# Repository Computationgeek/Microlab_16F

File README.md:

# MicroLab 16F - PIC16F877A Development Board  
A hand-soldered PIC16F877A development board built entirely on perfboard. This project was born from a desire to gain a deep understanding of embedded systems hardware by building everything from scratch - no pre-made modules, no shortcuts.

## Vision & Motivation

In 2026, most developers rely on modern MCUs like ESP32 and STM32. But there's something special about PIC microcontrollers - they force you to understand registers, bit manipulation, and hardware at a fundamental level: no HAL abstraction, no hand-holding.

I built MicroLab 16F because:
- **Learning by doing** - Soldering each connection taught me more than any tutorial
- **Legacy matters** - PIC16F877A is still widely used in education and industry
- **Maker ethos** - If you can't build it yourself, you don't truly understand it
- **Fun over perfection** - This isn't a product, it's a learning journey

## Features

### Hardware
- **PIC16F877A** microcontroller (40-pin DIP)
- **20MHz HS crystal** oscillator with 22pF load capacitors
- **Mini breadboard** integrated prototyping area
- **10kΩ potentiometer** connected to RA0 (ADC input)
- **Active buzzer** driven by BC547 NPN transistor on RD1
- **User-addressable LED** on RB0
- **Two tactile buttons** - User button (configurable) and Reset button (MCLR)
- **USB-C power input** with 5V regulation
- **PICkit3 programming header** (ICSP interface)
- **Labeled pin headers** for all GPIO ports (PORTA, PORTB, PORTC, PORTD, PORTE)

### Power System
- USB-C input with 5V output
- Dedicated power LED indicator
- Decoupling capacitors for stable operation
- External power compatible (PICkit3 or USB-C)

## Detailed Specifications

| Parameter | Value |
|-----------|-------|
| **Microcontroller** | PIC16F877A (Microchip) |
| **Architecture** | 8-bit RISC |
| **Program Memory** | 14.3 KB (8192 words) Flash |
| **RAM** | 368 bytes |
| **EEPROM** | 256 bytes |
| **Clock Frequency** | 20 MHz (HS Crystal) |
| **I/O Pins** | 33 |
| **ADC Channels** | 8 (10-bit resolution) |
| **Timers** | 3 (Timer0/1/2) |
| **PWM Channels** | 2 (CCP modules) |
| **Serial Interfaces** | USART, I²C, SPI |
| **Operating Voltage** | 5V DC |
| **Power Source** | USB-C (5V) |
| **Programming Interface** | ICSP (In-Circuit Serial Programming) |
| **Programmer** | PICkit3

## Components Used

### Main Components
| Component | Specification | Quantity | Purpose |
|-----------|---------------|----------|---------|
| PIC16F877A-I/P | 40-pin DIP | 1 | Main microcontroller |
| Crystal Oscillator | 20 MHz HC-49S | 1 | Clock source |
| Ceramic Capacitor | 22pF | 2 | Crystal load capacitors |
| Ceramic Capacitor | 100nF | 5+ | Decoupling/bypass |
| Electrolytic Capacitor | 10µF 16V | 2 | Power filtering |
| BC547 NPN Transistor | TO-92 | 1 | Buzzer driver |
| Active Buzzer | 5V | 1 | Audio output |
| LED (5mm) | Red/Green | 3 | Power, User, Status indicators |
| Resistor | 10kΩ | 5+ | Pull-ups, current limiting |
| Resistor | 330Ω | 3 | LED current limiting |
| Resistor | 1kΩ | 1 | Base resistor for BC547 |
| Potentiometer | 10kΩ linear | 1 | Analog input (RA0) |
| Tactile Switch | 6×6mm | 2 | User button, Reset button |
| Mini Breadboard | 170 points | 1 | Prototyping area |
| USB-C Connector | Breakout module | 1 | Power input |
| Pin Headers | 2.54mm pitch | Multiple | GPIO breakout |
| Perfboard | Single-sided | 1 | PCB substrate |
| IC Socket | 40-pin DIP | 1 | PIC mounting (optional) |

## Software & Tools

### Development Environment
- **IDE:** MPLAB X IDE v6.20 (Last version with PICkit3 support)
- **Compiler:** MPLAB XC8 v2.46 (Free edition)
- **Programmer:** PICkit3 In-Circuit Debugger/Programmer
- **OS:** Tested on Linux Mint 21.3 & Windows 10/11

### Programming Setup
```bash
# Linux users: Add udev rules for PICkit3
sudo nano /etc/udev/rules.d/26-microchip.rules

# Add this line:
SUBSYSTEM=="usb", ATTR{idVendor}=="04d8", ATTR{idProduct}=="900a", MODE="0666", GROUP="plugdev"

# Reload rules
sudo udevadm control --reload-rules
sudo udevadm trigger
```

### Configuration Bits (Standard Setup)
```c
#pragma config FOSC = HS        // High-Speed crystal oscillator
#pragma config WDTE = OFF       // Watchdog Timer disabled
#pragma config PWRTE = ON       // Power-up Timer enabled
#pragma config BOREN = ON       // Brown-out Reset enabled
#pragma config LVP = OFF        // Low-Voltage Programming disabled (CRITICAL for ICSP)
#pragma config CPD = OFF        // Data EEPROM Code Protection off
#pragma config WRT = OFF        // Flash Program Memory Write Enable off
#pragma config CP = OFF         // Flash Program Memory Code Protection off
```

## Getting Started

### 1. Power Up
Connect the USB-C cable to a 5V power source (laptop, power bank, or wall adapter).
The power LED should illuminate.

### 2. Connect Programmer
**PICkit3 Pinout (6-pin header):**
1 - MCLR  → PIC Pin 1 (MCLR/VPP)
2 - VDD   → PIC Pin 11, 32 (VDD) - For sensing only
3 - GND   → PIC Pin 12, 31 (VSS)
4 - PGD   → PIC Pin 40 (RB7/PGD)
5 - PGC   → PIC Pin 39 (RB6/PGC)
6 - NC    → Not connected

## Troubleshooting

### PICkit3 "Target VDD too low" Error
**Problem:** VDD measured as 4.75V instead of 5.0V during programming.

**Cause:** Board peripherals (buzzer, LEDs) draw more current than PICkit3 can supply (~30-50mA limit).

**Solution:** 
1. In MPLAB X: Project Properties → PICkit3 → Power → UNCHECK "Power target from tool"
2. Power board via USB-C only
3. PICkit3 is used for programming signals, not power

### Programming Fails at Address 0x0000
**Cause:** Incorrect config bits or MCLR circuit issue.

**Solution:**
- Ensure `LVP = OFF` in config bits
- Verify 10kΩ pull-up resistor on MCLR pin
- Try a slower programming speed in MPLAB X settings

See [docs/troubleshooting.md](docs/troubleshooting.md) for more.

## Learning Resources

### PIC16F877A Deep Dive
- [Microchip Official Datasheet](https://www.microchip.com/wwwproducts/en/PIC16F877A)
- [Gooligum Electronics PIC Tutorials](https://www.gooligum.com.au/PIC-tutorials) - Best assembly/register-level guide
- Microchip Application Notes: AN526 (Math routines), AN617 (Fixed-point math)

### Recommended Reading
- "PIC Microcontroller Project Book" by John Iovine
- "Programming PIC Microcontrollers with XC8" by Armstrong Subero
- Embedded.fm podcast episodes on PIC architecture

## Why PIC16F877A in 2026?

**Yes, it's 25+ years old. Here's why it still matters:**

1. **Educational Gold Standard** - Used in universities worldwide to teach embedded fundamentals
2. **Register-Level Programming** - No bloated HALs hiding what's actually happening
3. **Industry Workhorse** - Still found in industrial equipment, automotive, and legacy systems
4. **Simplicity** - 35 instructions vs 100+ in ARM Cortex
5. **Availability** - Cheap, plentiful, easy to source
6. **Hands-On Learning** - DIP package = breadboard/perfboard friendly

Modern isn't always better. Sometimes you need to go back to basics.

## License

MIT License - Build, modify, share freely. Just give credit.

## 🔗 Links

- **Build Story:** [Hackster.io Project](https://www.hackster.io/aamirayaaz5/building-a-pic16f877a-development-board-from-scratch-in-2026-7d29bc)
- **LinkedIn Post:** [LinkedIn Post about the board](https://www.linkedin.com/posts/aamir-ayaaz-b5549a220_embeddedsystems-electronicsengineering-hardwaredesign-activity-7425852984116404224-cy4W?utm_source=share&utm_medium=member_desktop&rcm=ACoAADeZ0vEBUnqS9fmuq7yIjKdyj92gUf-e6x0)

## Acknowledgments

Built with:
- Lots of solder fumes
- Multiple debugging sessions
- A stubborn refusal to give up when VDD dropped to 4.75V
- Coffee

**Special thanks to the PIC community and all the forum posts from 2005-2015 that saved this project.**

---

*"If you can't build it yourself, you don't truly understand it."*

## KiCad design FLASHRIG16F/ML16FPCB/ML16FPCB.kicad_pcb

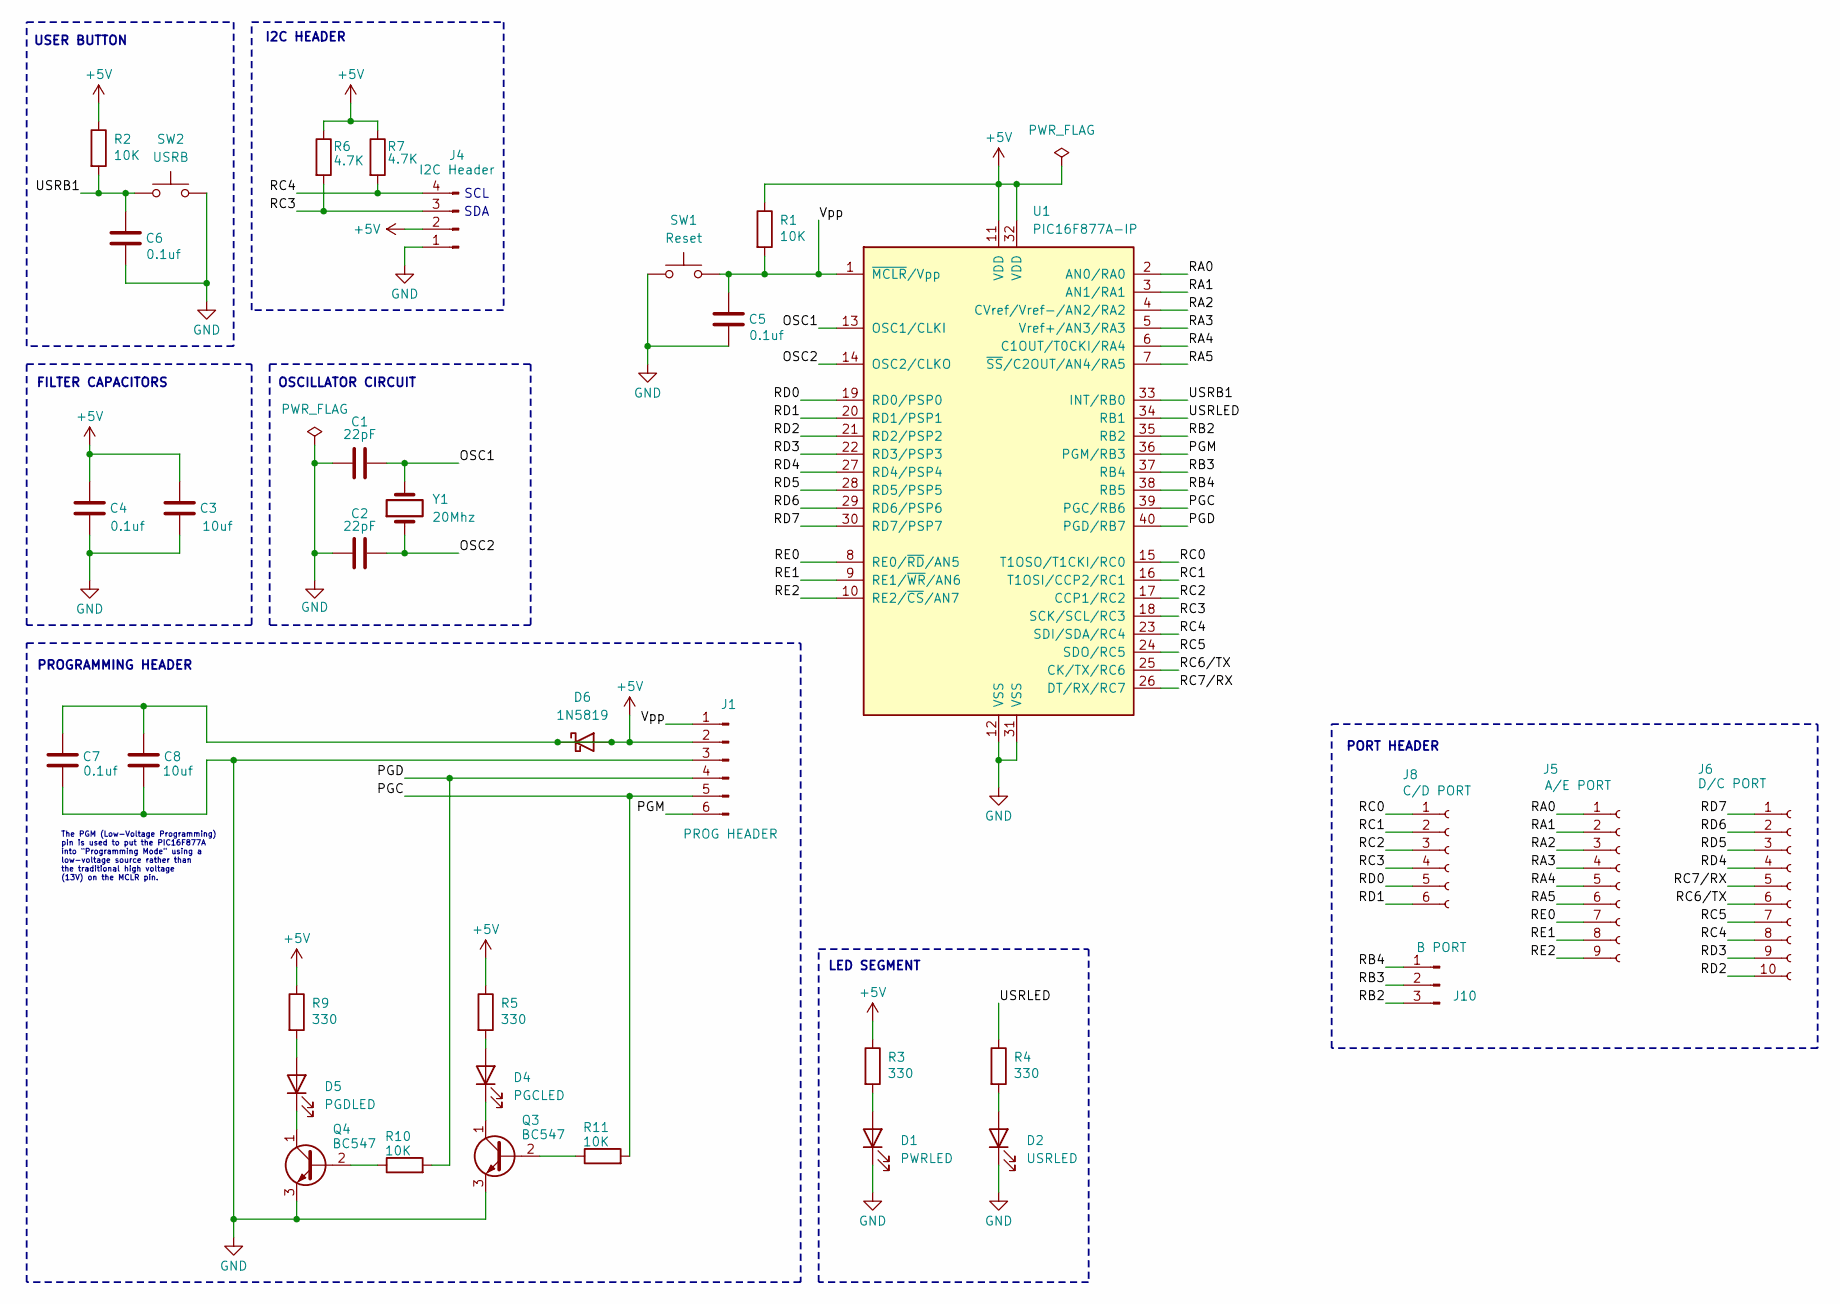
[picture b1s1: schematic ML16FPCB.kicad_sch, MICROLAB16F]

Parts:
C1, C2: 22pF; C_Disc_D3.0mm_W1.6mm_P2.50mm
C3, C8: 10uf; C_Radial_D5.0mm_H11.0mm_P2.00mm
C4, C5, C6, C7: 0.1uf; C_Disc_D3.0mm_W1.6mm_P2.50mm
D1: PWRLED; LED_D5.0mm
D2: USRLED; LED_D5.0mm
D4: PGCLED; LED_D5.0mm
D5: PGDLED; LED_D5.0mm
D6: 1N5819; D_DO-41_SOD81_P10.16mm_Horizontal
J1: PROG HEADER; PinHeader_1x06_P2.54mm_Vertical
J4: I2C Header; PinHeader_1x04_P2.54mm_Vertical
J5: A/E PORT; PinSocket_1x09_P2.54mm_Vertical
J6: D/C PORT; PinSocket_1x10_P2.54mm_Vertical
J8: C/D PORT; PinSocket_1x06_P2.54mm_Vertical
J10: B PORT; PinSocket_1x03_P2.54mm_Vertical
Q3, Q4: BC547; TO-92_Inline
R1, R2, R10, R11: 10K; R_Axial_DIN0207_L6.3mm_D2.5mm_P10.16mm_Horizontal
R3, R4, R5, R9: 330; R_Axial_DIN0207_L6.3mm_D2.5mm_P10.16mm_Horizontal
R6, R7: 4.7K; R_Axial_DIN0207_L6.3mm_D2.5mm_P10.16mm_Horizontal
SW1: Reset; SW_PUSH_6mm
SW2: USRB; SW_PUSH_6mm
U1: PIC16F877A-IP; 3M_Textool_240-1288-00-0602J_2x20_P2.54mm
Y1: 20Mhz; Crystal_HC49-U_Vertical

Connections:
+5V: C3.1, C4.1, C7.1, C8.1, D6.1 (K), D6.2 (A), J1.2, J4.2, R1.1, R2.1, R3.1, R5.1, R6.1, R7.1, R9.1, U1.11 (VDD), U1.32 (VDD)
/OSC1: C1.1, U1.13 (OSC1/CLKI), Y1.2
/OSC2: C2.2, U1.14 (OSC2/CLKO), Y1.1
/PGC: J1.5, R11.2, U1.39 (PGC/RB6)
/PGD: J1.4, R10.2, U1.40 (PGD/RB7)
/PGM: J1.6, U1.36 (PGM/RB3)
/RA0: J5.1, U1.2 (AN0/RA0)
/RA1: J5.2, U1.3 (AN1/RA1)
/RA2: J5.3, U1.4 (CVref/Vref-/AN2/RA2)
/RA3: J5.4, U1.5 (Vref+/AN3/RA3)
/RA4: J5.5, U1.6 (C1OUT/T0CKI/RA4)
/RA5: J5.6, U1.7 (~SS/C2OUT/AN4/RA5)
/RB2: J10.3, U1.35 (RB2)
/RB3: J10.2, U1.37 (RB4)
/RB4: J10.1, U1.38 (RB5)
/RC0: J8.1, U1.15 (T1OSO/T1CKI/RC0)
/RC1: J8.2, U1.16 (T1OSI/CCP2/RC1)
/RC2: J8.3, U1.17 (CCP1/RC2)
/RC3: J4.3, J8.4, R6.2, U1.18 (SCK/SCL/RC3)
/RC4: J4.4, J6.8, R7.2, U1.23 (SDI/SDA/RC4)
/RC5: J6.7, U1.24 (SDO/RC5)
/RC6/TX: J6.6, U1.25 (CK/TX/RC6)
/RC7/RX: J6.5, U1.26 (DT/RX/RC7)
/RD0: J8.5, U1.19 (RD0/PSP0)
/RD1: J8.6, U1.20 (RD1/PSP1)
/RD2: J6.10, U1.21 (RD2/PSP2)
/RD3: J6.9, U1.22 (RD3/PSP3)
/RD4: J6.4, U1.27 (RD4/PSP4)
/RD5: J6.3, U1.28 (RD5/PSP5)
/RD6: J6.2, U1.29 (RD6/PSP6)
/RD7: J6.1, U1.30 (RD7/PSP7)
/RE0: J5.7, U1.8 (RE0/~RD/AN5)
/RE1: J5.8, U1.9 (RE1/~WR/AN6)
/RE2: J5.9, U1.10 (RE2/~CS/AN7)
/USRB1: C6.1, R2.2, SW2.1, U1.33 (INT/RB0)
/USRLED: R4.1, U1.34 (RB1)
/Vpp: C5.1, J1.1, R1.2, SW1.2, U1.1 (~MCLR/Vpp)
GND: C1.2, C2.1, C3.2, C4.2, C5.2, C6.2, C7.2, C8.2, D1.1 (K), D2.1 (K), J1.3, J4.1, Q3.3 (E), Q4.3 (E), SW1.1, SW2.2, U1.12 (VSS), U1.31 (VSS)
unnamed: D1.2 (A), R3.2
unnamed: D2.2 (A), R4.2
unnamed: D4.2 (A), R5.2
unnamed: D4.1 (K), Q3.1 (C)
unnamed: D5.2 (A), R9.2
unnamed: D5.1 (K), Q4.1 (C)
unnamed: Q3.2 (B), R11.1
unnamed: Q4.2 (B), R10.1

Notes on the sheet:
I2C HEADER
OSCILLATOR CIRCUIT
FILTER CAPACITORS
LED SEGMENT
PROGRAMMING HEADER
SDA
The PGM (Low-Voltage Programming) pin is used to put the PIC16F877A into "Programming Mode" using a low-voltage source rather than the traditional high voltage (13V) on the MCLR pin.
USER BUTTON
PORT HEADER
SCL

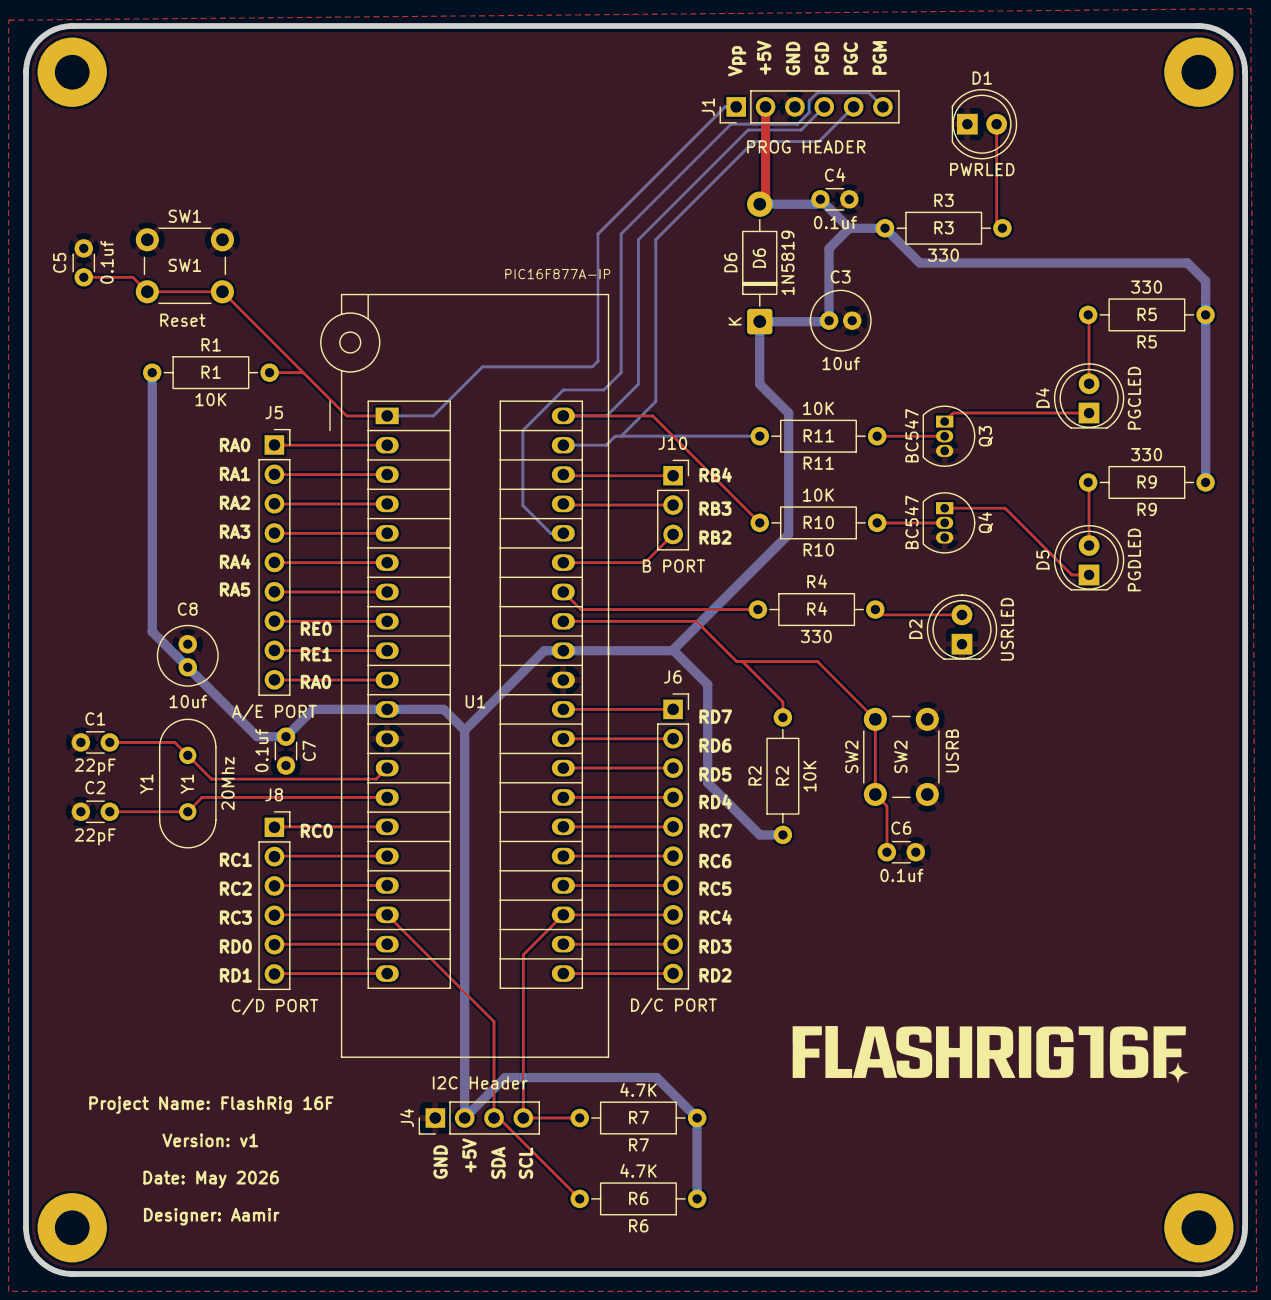
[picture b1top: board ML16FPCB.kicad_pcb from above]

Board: 2 copper layers, 105.5 x 108.0 mm, 35 parts (0 on the bottom side), 46 nets.

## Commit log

2026-04-24 Remove author attribution from README.md
    Removed attribution to Aamir Ayaaz from README.
2026-04-24 Add MIT License to the project
2026-04-24 Create Schematic
2026-05-07 Uploading FlashRig PCb project
